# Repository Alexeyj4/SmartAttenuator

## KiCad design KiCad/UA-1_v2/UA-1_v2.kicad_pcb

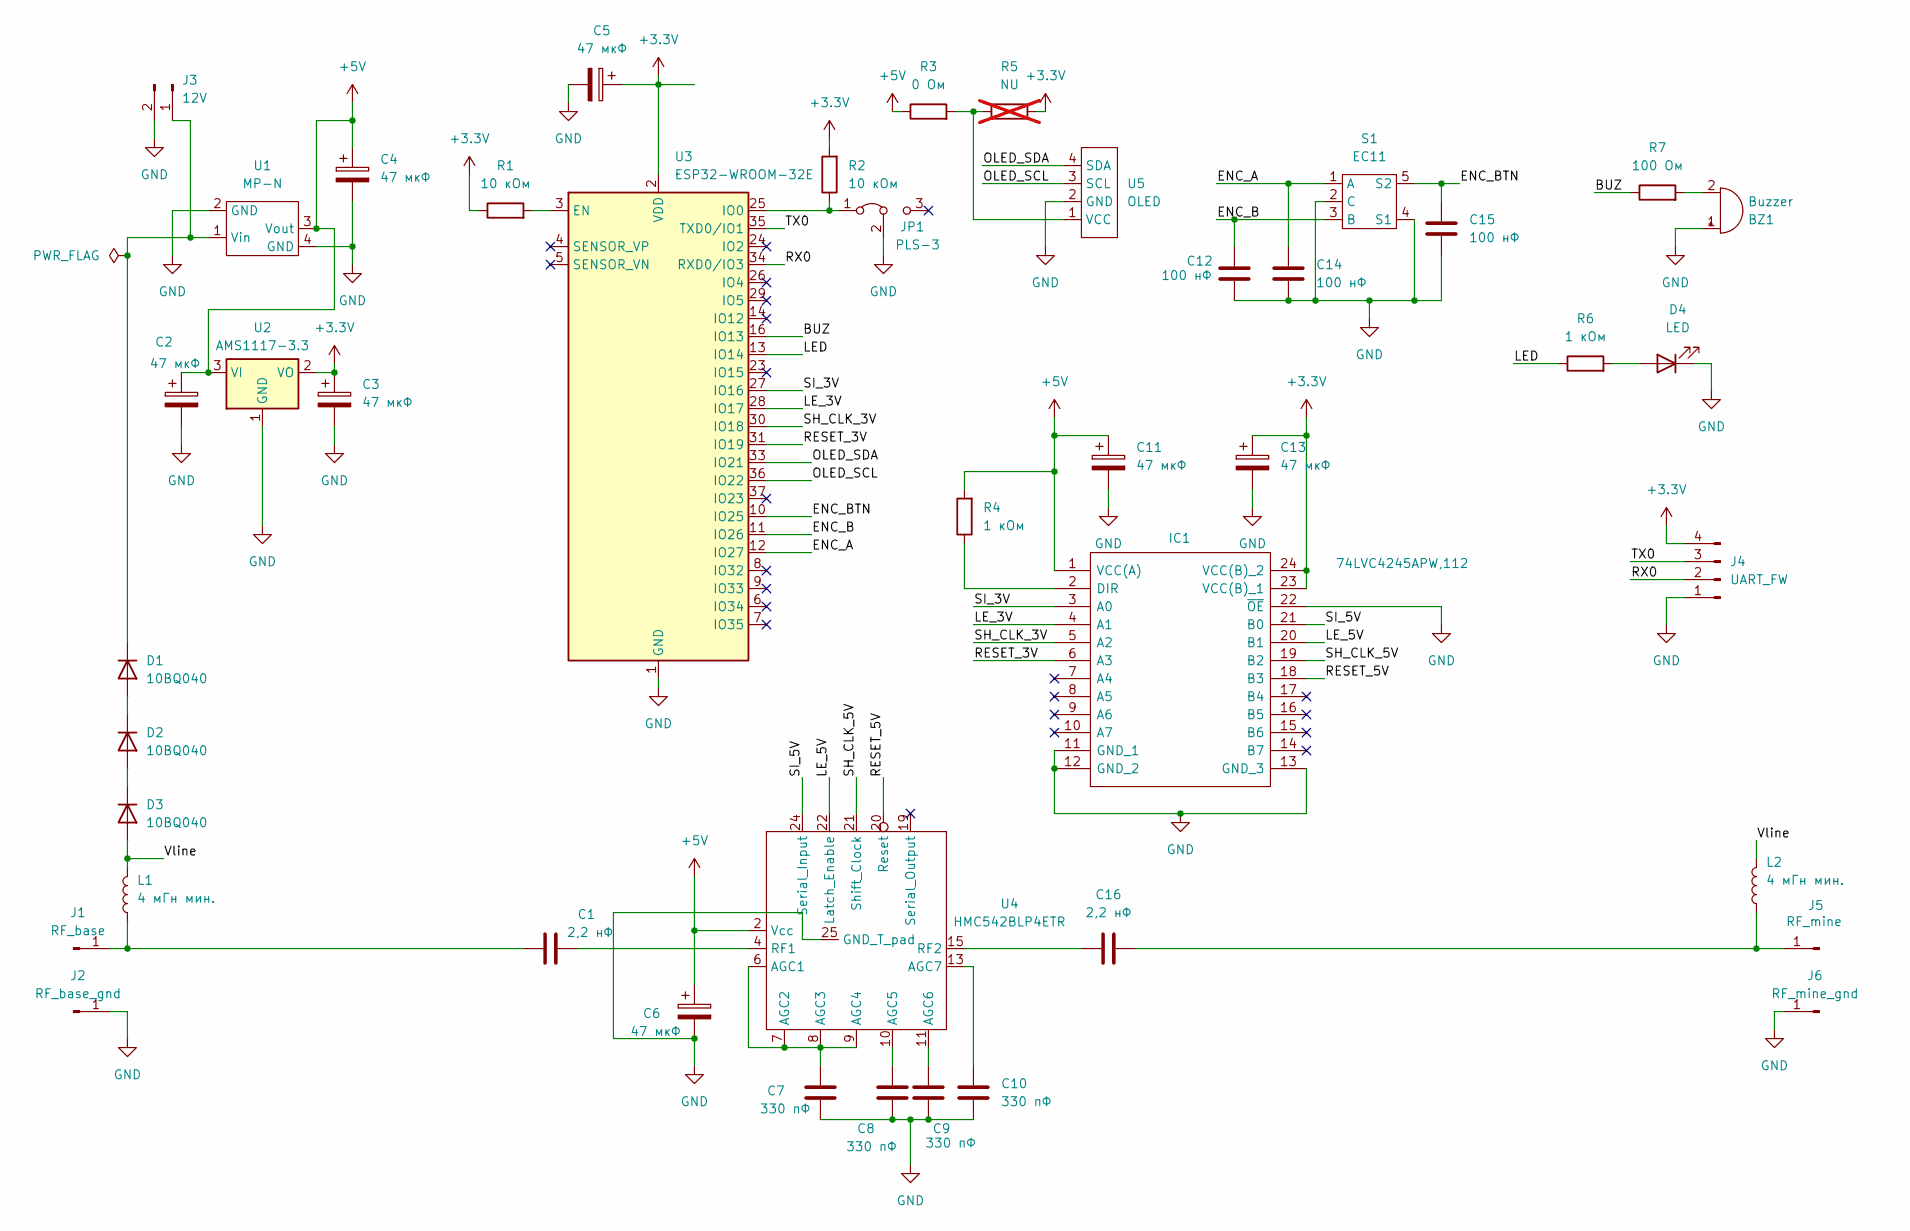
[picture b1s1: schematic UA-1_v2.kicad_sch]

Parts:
BZ1: Buzzer; HC0903A
C1, C16: 2,2 нФ; C_Disc_D7.5mm_W5.0mm_P10.00mm
C2, C3, C4, C5, C6, C11, C13: 47 мкФ; CP_EIA-7343-31_Kemet-D_Pad2.25x2.55mm_HandSolder
C7, C8, C9, C10: 330 пФ; C_0805_2012Metric_Pad1.18x1.45mm_HandSolder
C12, C14, C15: 100 нФ; C_0805_2012Metric_Pad1.18x1.45mm_HandSolder
D1, D2, D3: 10BQ040; D_SMB_Handsoldering
D4: LED; LED_1206_3216Metric_Pad1.42x1.75mm_HandSolder
IC1: 74LVC4245APW,112; SOP65P640X110-24N; Manufacturer_Part_Number 74LVC4245APW,112; Mouser Part Number 771-LVC4245APW112
J1: RF_base; TestPoint_Pad_1.0x1.0mm
J2: RF_base_gnd; TestPoint_Pad_1.0x1.0mm
J3: 12V; JST_PH_B2B-PH-K_1x02_P2.00mm_Vertical
J4: UART_FW; PinHeader_1x04_P2.54mm_Vertical
J5: RF_mine; TestPoint_Pad_1.0x1.0mm
J6: RF_mine_gnd; TestPoint_Pad_1.0x1.0mm
JP1: PLS-3; PinHeader_1x03_P2.54mm_Vertical
L1, L2: 4 мГн мин.; L_Axial_L24.0mm_D7.1mm_P30.48mm_Horizontal_Vishay_IM-10-28
R1, R2: 10 кОм; R_0805_2012Metric_Pad1.20x1.40mm_HandSolder
R3: 0 Ом; R_0805_2012Metric_Pad1.20x1.40mm_HandSolder
R4, R6: 1 кОм; R_0805_2012Metric_Pad1.20x1.40mm_HandSolder
R5: NU; R_0805_2012Metric_Pad1.20x1.40mm_HandSolder; not fitted
R7: 100 Ом; R_0805_2012Metric_Pad1.20x1.40mm_HandSolder
S1: EC11; RotaryEncoder EC11 SMD
U1: MP-N; MPN
U2: AMS1117-3.3; SOT-223-3_TabPin2
U3: ESP32-WROOM-32E; ESP32-WROOM-32D
U4: HMC542BLP4ETR; QFN-24-1EP_4x4mm_P0.5mm_EP2.6x2.6mm_ThermalVias
U5: OLED; OLED I2C

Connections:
+3.3V: C3.1, C5.1, C13.1, IC1.23 (VCC(B)_1), IC1.24 (VCC(B)_2), J4.4, R1.1, R2.2, R5.2, U2.2 (VO), U3.2 (VDD)
+5V: C2.1, C4.1, C6.1, C11.1, IC1.1 (VCC(A)), R3.1, R4.2, U1.3 (Vout), U2.3 (VI), U4.2 (Vcc)
/BUZ: R7.1, U3.16 (IO13)
/ENC_A: C14.1, S1.1 (A), U3.12 (IO27)
/ENC_B: C12.1, S1.3 (B), U3.11 (IO26)
/ENC_BTN: C15.1, S1.5 (S2), U3.10 (IO25)
/LED: R6.1, U3.13 (IO14)
/LE_3V: IC1.4 (A1), U3.28 (IO17)
/LE_5V: IC1.20 (B1), U4.22 (Latch_Enable)
/OLED_SCL: U3.36 (IO22), U5.3 (SCL)
/OLED_SDA: U3.33 (IO21), U5.4 (SDA)
/RESET_3V: IC1.6 (A3), U3.31 (IO19)
/RESET_5V: IC1.18 (B3), U4.20 (Reset)
/RX0: J4.2, U3.34 (RXD0/IO3)
/SH_CLK_3V: IC1.5 (A2), U3.30 (IO18)
/SH_CLK_5V: IC1.19 (B2), U4.21 (Shift_Clock)
/SI_3V: IC1.3 (A0), U3.27 (IO16)
/SI_5V: IC1.21 (B0), U4.24 (Serial_Input)
/TX0: J4.3, U3.35 (TXD0/IO1)
/Vline: D3.2 (A), L1.2, L2.2
GND: BZ1.1 (+), C2.2, C3.2, C4.2, C5.2, C6.2, C7.2, C8.2, C9.2, C10.2, C11.2, C12.2, C13.2, C14.2, C15.2, D4.1 (K), IC1.11 (GND_1), IC1.12 (GND_2), IC1.13 (GND_3), IC1.22 (~OE), J2.1, J3.2, J4.1, J6.1, JP1.2 (C), S1.2 (C), S1.4 (S1), U1.2 (GND), U1.4 (GND), U2.1 (GND), U3.1 (GND), U3.15 (GND), U3.38 (GND), U3.39 (GND), U4.25 (GND_T_pad), U5.2 (GND)
unnamed: BZ1.2 (-), R7.2
unnamed: D1.2 (A), D2.1 (K)
unnamed: D1.1 (K), J3.1, U1.1 (Vin)
unnamed: D2.2 (A), D3.1 (K)
unnamed: D4.2 (A), R6.2
unnamed: IC1.2 (DIR), R4.1
unnamed: C1.2, J1.1, L1.1
unnamed: C16.1, J5.1, L2.1
unnamed: JP1.1 (A), R2.1, U3.25 (IO0)
unnamed: R1.2, U3.3 (EN)
unnamed: C7.1, U4.6 (AGC1), U4.7 (AGC2), U4.8 (AGC3), U4.9 (AGC4)
unnamed: C8.1, U4.10 (AGC5)
unnamed: C9.1, U4.11 (AGC6)
unnamed: C10.1, U4.13 (AGC7)
unnamed: C1.1, U4.4 (RF1)
unnamed: C16.2, U4.15 (RF2)
unnamed: R3.2, R5.1, U5.1 (VCC)

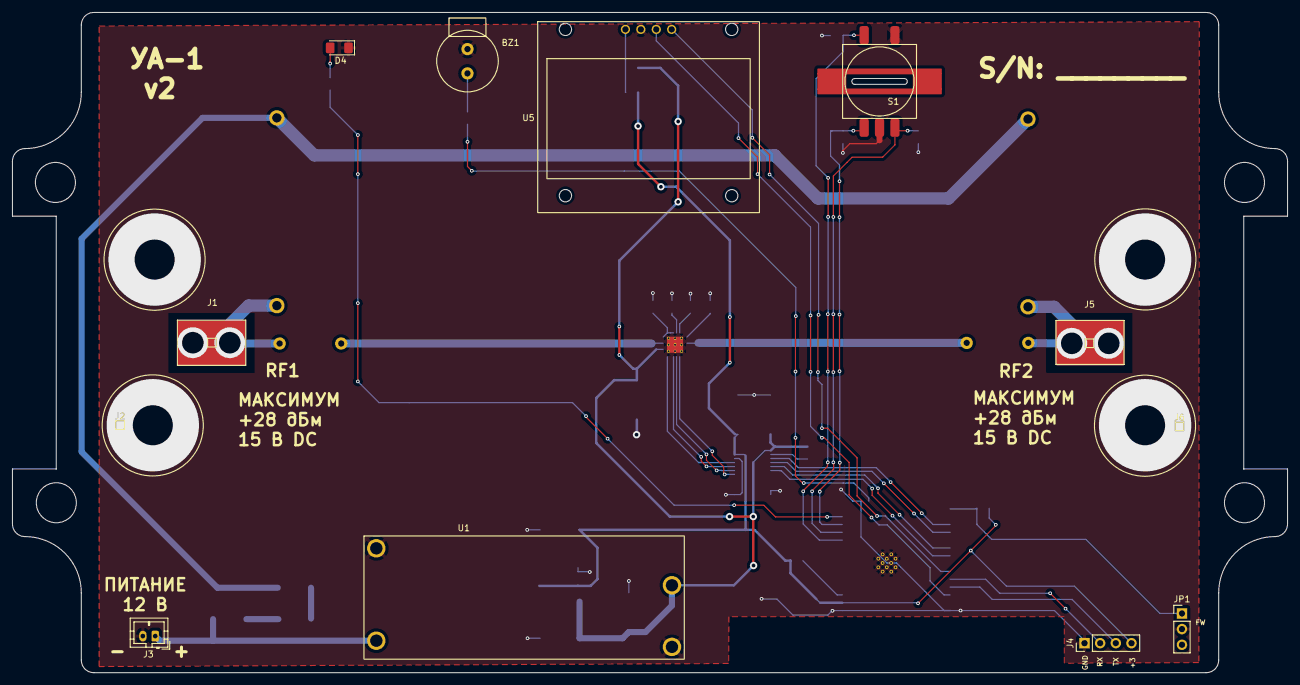
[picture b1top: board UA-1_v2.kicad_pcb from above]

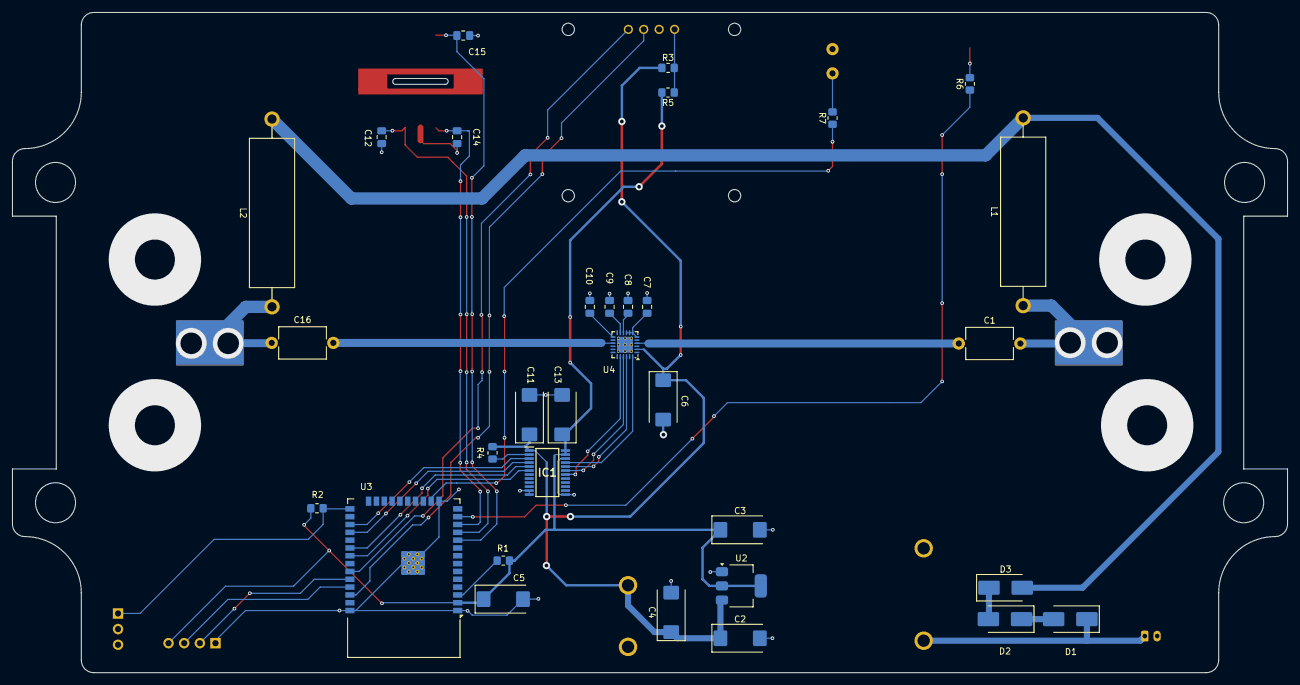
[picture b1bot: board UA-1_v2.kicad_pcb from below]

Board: 2 copper layers, 207.0 x 107.2 mm, 44 parts (32 on the bottom side), 38 nets.

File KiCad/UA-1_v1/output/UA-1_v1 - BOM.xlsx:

Идентиф. | Обозначение | Посад.место | Количество | Значение
1 | U1 | MPN | 1 | MP-N
2 | U5 | OLED I2C | 1 | OLED
3 | J2 | TestPoint_Pad_1.0x1.0mm | 1 | RF_base_gnd
4 | BZ1 | HC0903A | 1 | Buzzer
5 | J5 | TestPoint_Pad_1.0x1.0mm | 1 | RF_mine
6 | J1 | TestPoint_Pad_1.0x1.0mm | 1 | RF_base
7 | D4 | LED_1206_3216Metric_Pad1.42x1.75mm_HandSolder | 1 | LED
8 | S1 | RotaryEncoder EC11 SMD | 1 | EC11
9 | J6 | TestPoint_Pad_1.0x1.0mm | 1 | RF_mine_gnd
10 | J3 | JST_PH_B2B-PH-K_1x02_P2.00mm_Vertical | 1 | 12V
11 | J4 | PinHeader_1x04_P2.54mm_Vertical | 1 | UART_FW
12 | R4,R6 | R_0805_2012Metric_Pad1.20x1.40mm_HandSolder | 2 | 1 кОм
13 | D1,D3,D2 | D_SMB_Handsoldering | 3 | 10BQ040
14 | C14,C15,C12 | C_0805_2012Metric_Pad1.18x1.45mm_HandSolder | 3 | 100 нФ
15 | C16,C1 | C_Disc_D7.5mm_W5.0mm_P10.00mm | 2 | 2,2 нФ
16 | C5,C11,C4,C2,C13,C6,C3 | CP_EIA-7343-31_Kemet-D_Pad2.25x2.55mm_HandSolder | 7 | 47 мкФ
17 | R3 | R_0805_2012Metric_Pad1.20x1.40mm_HandSolder | 1 | 0 Ом
18 | C9,C8,C10,C7 | C_0805_2012Metric_Pad1.18x1.45mm_HandSolder | 4 | 330 пФ
19 | R1,R2 | R_0805_2012Metric_Pad1.20x1.40mm_HandSolder | 2 | 10 кОм
20 | U3 | ESP32-WROOM-32D | 1 | ESP32-WROOM-32E
21 | U2 | SOT-223-3_TabPin2 | 1 | AMS1117-3.3
22 | U4 | QFN-24-1EP_4x4mm_P0.5mm_EP2.6x2.6mm_ThermalVias | 1 | HMC542BLP4ETR
23 | R7 | R_0805_2012Metric_Pad1.20x1.40mm_HandSolder | 1 | 100 Ом
24 | L1,L2 | L_Axial_L24.0mm_D7.1mm_P30.48mm_Horizontal_Vishay_IM-10-28 | 2 | 4 мГн мин.
25 | IC1 | SOP65P640X110-24N | 1 | 74LVC4245APW,112
26 | R5 | R_0805_2012Metric_Pad1.20x1.40mm_HandSolder | 1 | NU

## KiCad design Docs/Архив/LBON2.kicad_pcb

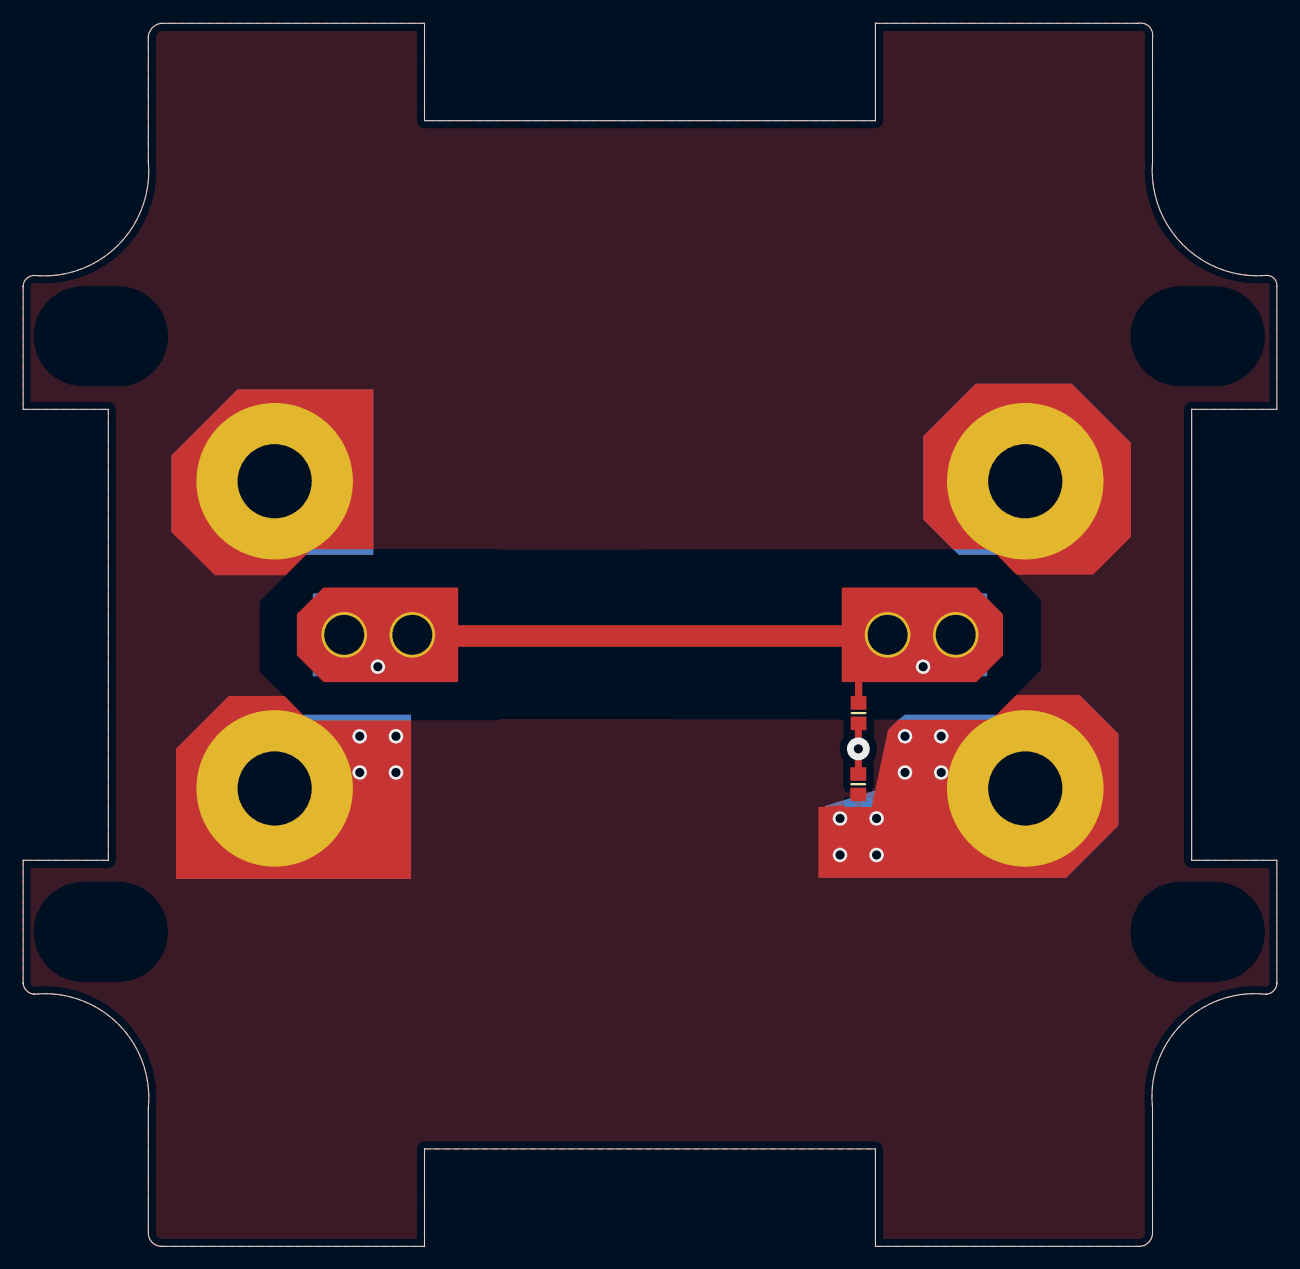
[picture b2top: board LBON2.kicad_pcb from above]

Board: 2 copper layers, 109.9 x 107.2 mm, 6 parts (0 on the bottom side), 2 nets.

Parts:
C1: 10N; 6-0805_N
J8, J9, J16, J17: CON1; VIA
R1: 75/50; 6-0805_N

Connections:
GND: J8.1, J9.1, J16.1, J17.1, R1.1
N44326: C1.1, R1.2

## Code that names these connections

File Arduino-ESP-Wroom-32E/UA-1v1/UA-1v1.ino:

#define OLED_DISPLAY_TYPE 1106
#include <Oled.h>
#include <ESP32Encoder.h>

#define BUZZER_PIN 13
#define LED_PIN 14
#define SI_3V_PIN 16
#define LE_3V_PIN 17
#define SH_CLK_3V_PIN 18
#define RESET_3V_PIN 19
//#define OLED_SDA_PIN 21
//#define OLED_SCL_PIN 22
#define ENC_BTN_PIN 25
#define ENC_B_PIN 26
#define ENC_A_PIN 27

Oled oled;
ESP32Encoder enc;

void setup() {
  // put your setup code here, to run once: 
  Serial.begin(115200);
  oled.begin(); 
  pinMode(LED_PIN,OUTPUT);
  pinMode(ENC_A_PIN, INPUT_PULLUP);
  pinMode(ENC_B_PIN, INPUT_PULLUP);
  pinMode(ENC_BTN_PIN, INPUT_PULLUP);
  pinMode(BUZZER_PIN, OUTPUT);
  enc.attachFullQuad(ENC_A_PIN, ENC_B_PIN);

}

void beep(){
  for(int i=0;i<200;i++){    
    digitalWrite(BUZZER_PIN,1);
    delay(1);
    digitalWrite(BUZZER_PIN,0);    
    delay(1);
  }
}

void loop() {
  // put your main code here, to run repeatedly:
  digitalWrite(LED_PIN,1);
  delay(500);
  digitalWrite(LED_PIN,0);
  delay(500);
  int enc_pos=-floor(enc.getCount()/2);
  Serial.println(enc_pos);
  oled.print(0,String(enc_pos));  
  oled.update();
  
  if(digitalRead(ENC_BTN_PIN)==0){
    Serial.println("key pressed");
    beep();
  }
  
}

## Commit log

2024-04-15 added datasheets
2024-04-23 added lbon source
2024-04-24 schemetic begin
2024-04-25 schematic finished. Need footprint to be added
2024-04-25 contur added
2024-04-26 pochti zakonchil razvodku
2024-04-27 finish pcb. Printing on paper
2024-04-27 fix mpn gnd-5v. fix C 5-10mm
2024-05-21 released beta w/o ble
2024-05-21 released beta with bt
2024-05-21 beta release with BT and define BT on off
2024-05-22 binarniks added
2024-05-23 add pls1-3
2024-07-09 v2 prod
2024-07-18 led on
2024-07-22 photo
